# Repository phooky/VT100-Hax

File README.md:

VT100 Hax for Retrocomp 2014
============================

I'm reverse engineering the VT100 firmware and adding some patches
for the 2014 retrocomp. It's crazy and fun!

Quick guide:
------------

* 23-0???.bin - raw dumps of the ROMs on the basic video board.
  These are four 2Kx8 ROMs; a single 8Kx8 version exists as well.
* basic.bin - combined ROM generated by concatenating the 2Kx2 ROMs.
* basic.d80 - disassembled basic ROM `dz80 -80 basic.bin`

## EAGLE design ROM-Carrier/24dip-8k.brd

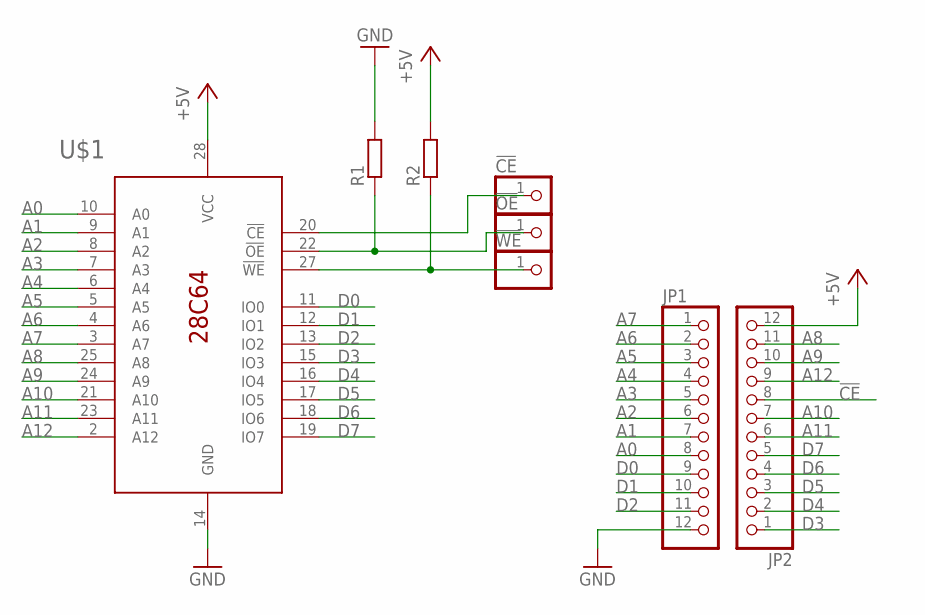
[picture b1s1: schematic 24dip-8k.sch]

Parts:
!CE: PINHD-1X1; 1X01
!OE: PINHD-1X1; 1X01
!WE: PINHD-1X1; 1X01
JP1, JP2: PINHD-1X12; 1X12
R1, R2: R-EU_R1206; R1206
U$1: AT28C64B28S; SO28W

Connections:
!CE: !CE.1, JP2.8, U$1.20 (!CE)
+5V: JP2.12, R2.2, U$1.28 (VCC)
A0: JP1.8, U$1.10 (A0)
A1: JP1.7, U$1.9 (A1)
A2: JP1.6, U$1.8 (A2)
A3: JP1.5, U$1.7 (A3)
A4: JP1.4, U$1.6 (A4)
A5: JP1.3, U$1.5 (A5)
A6: JP1.2, U$1.4 (A6)
A7: JP1.1, U$1.3 (A7)
A8: JP2.11, U$1.25 (A8)
A9: JP2.10, U$1.24 (A9)
A10: JP2.7, U$1.21 (A10)
A11: JP2.6, U$1.23 (A11)
A12: JP2.9, U$1.2 (A12)
D0: JP1.9, U$1.11 (IO0)
D1: JP1.10, U$1.12 (IO1)
D2: JP1.11, U$1.13 (IO2)
D3: JP2.1, U$1.15 (IO3)
D4: JP2.2, U$1.16 (IO4)
D5: JP2.3, U$1.17 (IO5)
D6: JP2.4, U$1.18 (IO6)
D7: JP2.5, U$1.19 (IO7)
GND: JP1.12, R1.2, U$1.14 (GND)
unnamed: !WE.1, R2.1, U$1.27 (!WE)
unnamed: !OE.1, R1.1, U$1.22 (!OE)

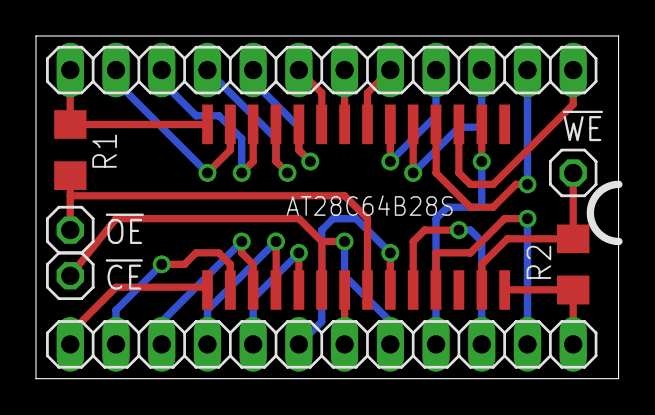
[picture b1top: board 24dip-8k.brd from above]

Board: 2 copper layers, 32.4 x 19.0 mm, 8 parts (0 on the bottom side), 26 nets.

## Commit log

2014-07-01 early notes; dumped E40-E56 ROMs
2014-07-01 giving the various ROMs their proper names instead of arbitrary socket locations
2014-07-01 created composite rom for basic board; adding disassembly
2014-07-01 adding readme
2014-07-03 adding ROM carrier board design
2014-07-04 * fix edge case of disassembler * update doc
2014-07-04 * Adding makefile for assembly and testing asm (ensure that the disassembled code reassembled matches the source binary)
2014-07-04 adding hacked rom
2014-07-04 * improve makefile matching rule and output naming * start labelling haxrom.d80 * automatically 0-pad output to 8k
2014-07-04 * commented checksum in disassembled binary * implemented checksum in python and confirmed on all ROMs
2014-07-04 * finish documenting checksum
2014-07-06 more haxrom.d80 documentation adding start of QT emulator
2014-07-06 adding z80sim code to build
2014-07-06 Simulator partially integrated
2014-07-06 slowly tying simulator and display together
2014-07-06 show read location on io_in rough comments on memory test
2014-07-07 started to document the flags buffer at last
2014-07-08 added start/stop fn
2014-07-09 a lot of tracing through asm. RE is hard.
2014-07-09 figured out what a memmove looks like
2014-07-09 recast code as data
2014-07-09 found the wait message.
2014-07-09 teased out another data segment
2014-07-09 getting into the weeds here
2014-07-09 I think we've teased out the NVR read and address code.
2014-07-10 NVR addressing working (sorta)
2014-07-11 debug prints
2014-07-12 starting in on keyboard interrupt stuff
2014-07-16 current state of qt mess
2014-07-16 starting on non-qt version
2014-07-17 rough cdk skeleton
2014-07-18 fix carrier board (was 24-9, needed to be 24-6) removed unnecessary z80 support from 8080 sim
2014-07-18 more cleanup; strip down sim to bones
2014-07-20 moved to ncurses; adding reg and mem dsply
2014-07-20 video display and interrupts chugging; we can get to set-up now
2014-07-20 emulator keypresses working; can do setup
2014-07-20 renaming cdk to ncurses
2014-07-21 added status bar, LEDs
2014-07-22 add display of status info (run/stop, control/typing)
2014-07-22 added control mode switches
2014-07-22 adding shift, causing problems adding bp ui
2014-07-22 shift key now working disabled breakpoints until they can be sensible
2014-07-22 breakpoint adding and removing
2014-07-22 starting in on memory display work
2014-07-23 added memory marking
2014-07-23 find location of setup area added memory column notation
2014-07-25 added command line parsing
2014-07-25 modified the old prom dumper to program the rom carriers
2014-07-26 rom burner working
2014-07-27 improved checksum to cover 8K roms
2014-07-27 converting into strings
2014-07-28 display breakpoints, add box
2014-07-28 display out port 0x42 (brightness)
2014-07-28 breaking out table into proper data
2014-07-28 removing checksum!
2014-07-28 using esc key instead of f2 for mode switching
2014-07-29 fixed constant/tag confusion
2014-07-31 working pusart implemented; talks to a linux pty
2014-07-31 added trace for breakpoints
2014-07-31 finding jump tables
2014-07-31 more cleanup, revert to standard setup message; time to get serious
2014-07-31 actually writing the screensaver. wow.
2014-07-31 ... and we have a hacked-up working screensaver.
2014-08-01 attempt #2
2014-08-01 ... aaand it works. Hooray. Everyone wins!
2014-08-02 adjust timeout to five minutes
2014-08-02 added mystery rom
2014-12-24 Default NVRAM contents
2014-12-24 Save default NVRAM contents
2014-12-24 Obey XON/XOFF flow control from VT100
2014-12-24 Adjust -r to switch to Typing mode too
2014-12-24 Fork off a shell on our new pty.
2014-12-24 Slow down CPU processing to 1MHz
    This makes the VT100 flash it's cursor and process characters at about
    the right speed. The CPU can accept characters at about 4800baud without
    flow control which matches other documentation.
    This is despite other documentation that says the CPU runs at 2.765 MHz.
    The key debounce routine is eating repeat codes though.
2014-12-24 More keyboard codes available.
    Make some explicit mappings for Function keys that don't exist on the
    VT100
    F5 - Linefeed (Return sends ^M)
    F6 - Escape KEY (rather than Ctrl-[)
    F7 - BREAK
    F9 - Shift-BREAK
2014-12-24 Adjust display look
    VT100 screen is set to green,
    VT Graphics has a good chance of working.
    Make the LED colours a bit more obvious (and flip ONLINE/LOCAL)
2015-01-08 Adjust alarm timer interval
2015-01-10 Clear some environment
    The LANG variable should be "C" or "POSIX", this is normally the default.
    The TERM we are emulating is a real VT100, of course.
2015-01-10 Fix CR vs NL problem.
    Curses has is poorly documented "nonl()" function.
    Note F5 is now available for something else.
2015-01-10 Default AM to on in the setup.
2015-01-11 Default NVRAM, turn off "keyclick"
2015-01-11 Flash comment
2015-01-11 Simulate double width with double space
2015-01-11 Decode DC012 control codes.
    Includes the Screen reverse toggle, the soft scroll latch, basic attribute
    configuration, blinking and vertical interrupt ACK.
    Add reverse video display.
2015-01-11 Keyboard note
2015-01-11 Part 1 of beeper
2015-01-11 Platform Notes
2015-01-11 Soft scroll highlighting
2015-01-11 Enable AVO and decode.
    The flag to enable AVO for the ROM is turned on, the GPO flag is turned off.
    AVO has been enabled by default and the Video display adjusted to show the
    extra attributes.
    Also a command line option has been added to turn off AVO.
2015-01-11 Explicit support for unicode curses.
    This looks really ugly; but it seems this is how your supposed to do it.
2015-03-01 Delay startup of shell until the VT100 is ready.
    This prevents problems with the flow control being non-operational
    during bootup.
2016-05-09 update version on eagle file
2016-05-09 fixed filename
2016-05-09 program->burn in makefile pin mappings to use a promdate instead of a shit ton of custom wiring
2016-05-09 provide power and choose external ports for burning
2016-05-09 change to 10 minute timeout
2016-05-09 fix extra pins
2016-08-24 Improve handling of keyboard, cursor and beeper
    The cursor flash rate depends on the keyboard TX rate so make sure that
    it's limited correctly. This means that beep updates will be generated
    at the correct rate too; it appears that 48 are sent for a normal beep
    so ignore that many repeats. Which gets exact beep recreation.
    This showed that the 'alarm' generated timing wasn't sufficiently accurate
    so that's been replaced by timing based on the vertical refresh emulation.
2017-01-17 Fix formatting in platform notes
2017-01-17 Fix formatting
2017-01-17 Screen saver variable names in fixed-width font
2017-01-17 Format section heading
2017-01-17 Format screen memory layout
2017-01-17 Clarify NVRAM interactions
2017-01-17 Format convenience functions
2017-01-17 Format LXI list
